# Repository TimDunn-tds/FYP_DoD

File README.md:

# FYP_DoD
Disk-on-disk FYP files.

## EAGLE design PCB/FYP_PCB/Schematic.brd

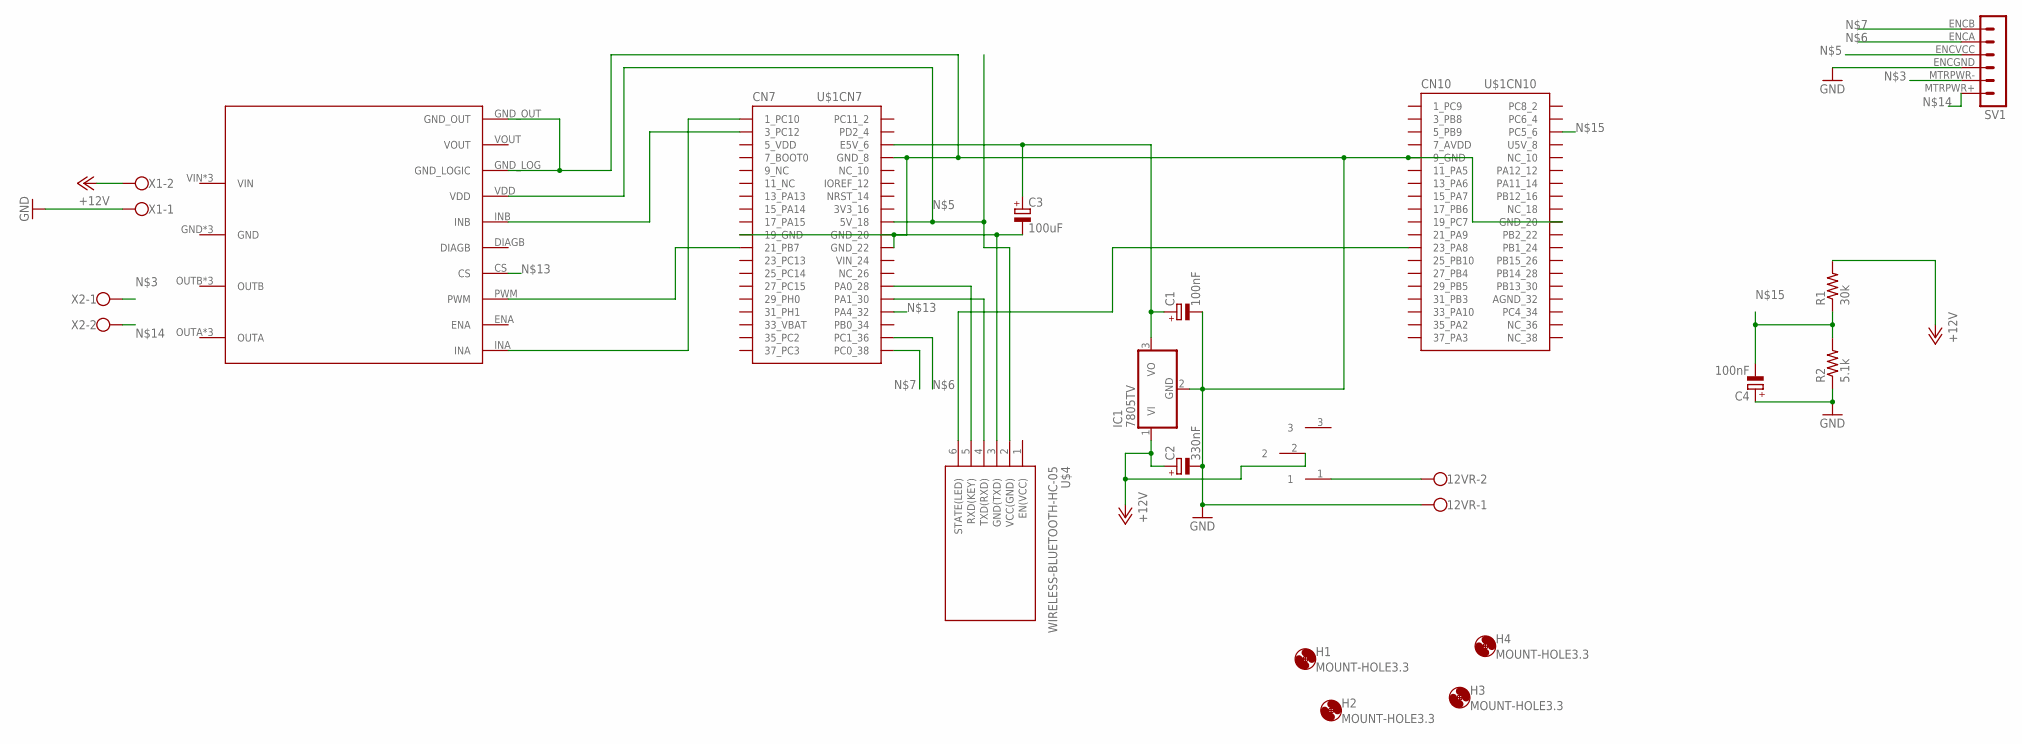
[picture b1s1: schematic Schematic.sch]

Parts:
12VR: W237-102
C1, C4: 100nF; E2,5-5
C2: 330nF; E2,5-5
C3: 100uF; E2,5-5
H1, H2, H3, H4: MOUNT-HOLE3.3; 3,3
IC1: 7805TV; TO220V
R1: 30k; 0204/7
R2: 5.1k; 0204/7
SV1: MA06-1
U$1: NUCLEO-SHIELD-20PIN; NUCLEO-SHIELD-UNDERSIDE-SHORT-20-PINHEADER
U$2: VNH5019REAL; MULTIPOWERSO-302
U$3: TOGGLESWITCH
U$4: WIRELESS-BLUETOOTH-HC-05
X1, X2: W237-102

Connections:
+12V: C2.+, IC1.1 (VI), R1.2, U$3.2, X1.2
EN(VCC): U$4.1 (EN(VCC))
GND: 12VR.1, C1.-, C2.-, C3.-, C4.+, IC1.2 (GND), R2.1, SV1.ENCGND, U$1.CN7_8 (GND_8), U$1.CN7_19 (19_GND), U$1.CN7_20 (GND_20), U$1.CN7_22 (GND_22), U$1.CN10_9 (9_GND), U$1.CN10_20 (GND_20), U$2.GND_LOG (GND_LOGIC), U$2.GND_OUT, U$4.3 (GND(TXD)), X1.1
unnamed: U$1.CN7_1 (1_PC10), U$2.INA
unnamed: U$1.CN7_21 (21_PB7), U$2.PWM
unnamed: SV1.MTRPWR-, X2.1
unnamed: U$1.CN7_3 (3_PC12), U$2.INB
unnamed: SV1.ENCVCC, U$1.CN7_18 (5V_18), U$2.VDD, U$4.2 (VCC(GND))
unnamed: SV1.ENCA, U$1.CN7_36 (PC1_36)
unnamed: SV1.ENCB, U$1.CN7_38 (PC0_38)
unnamed: 12VR.2, U$3.1
unnamed: U$1.CN7_30 (PA1_30), U$4.4 (TXD(RXD))
unnamed: C1.+, C3.+, IC1.3 (VO), U$1.CN7_6 (E5V_6)
unnamed: U$1.CN7_28 (PA0_28), U$4.5 (RXD(KEY))
unnamed: U$1.CN10_23 (23_PA8), U$4.6 (STATE(LED))
unnamed: U$1.CN7_32 (PA4_32), U$2.CS
unnamed: SV1.MTRPWR+ (MTRPWR), X2.2
unnamed: C4.-, R1.1, R2.2, U$1.CN10_6 (PC5_6)

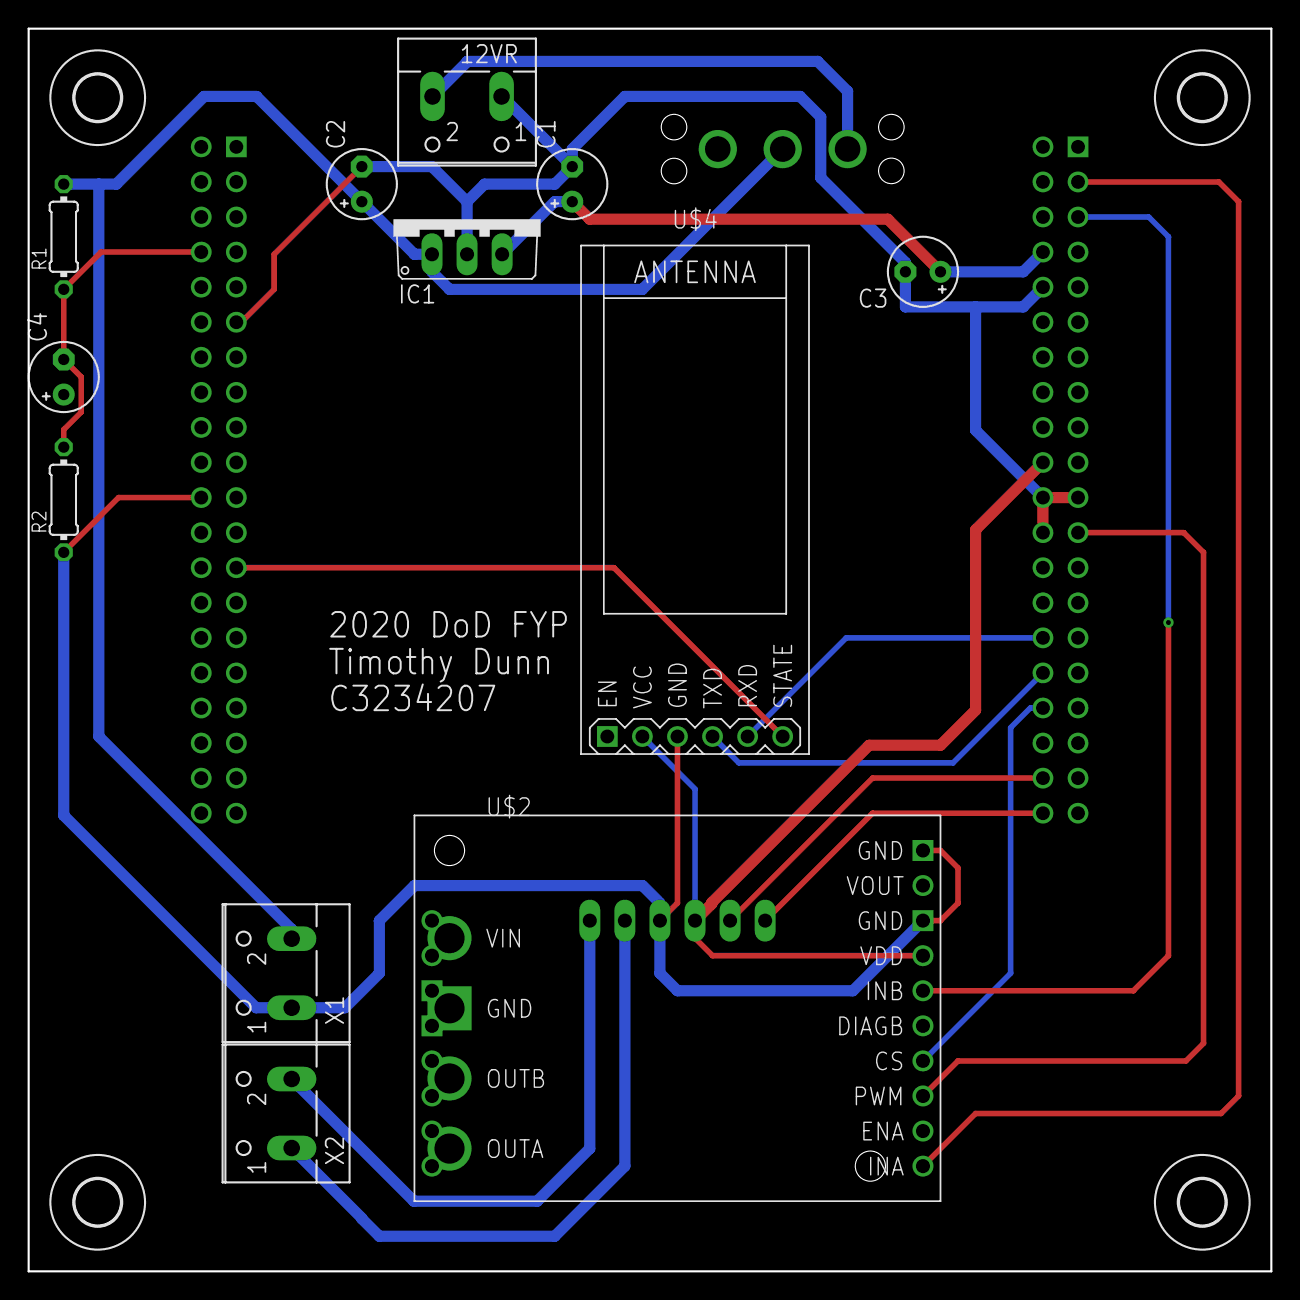
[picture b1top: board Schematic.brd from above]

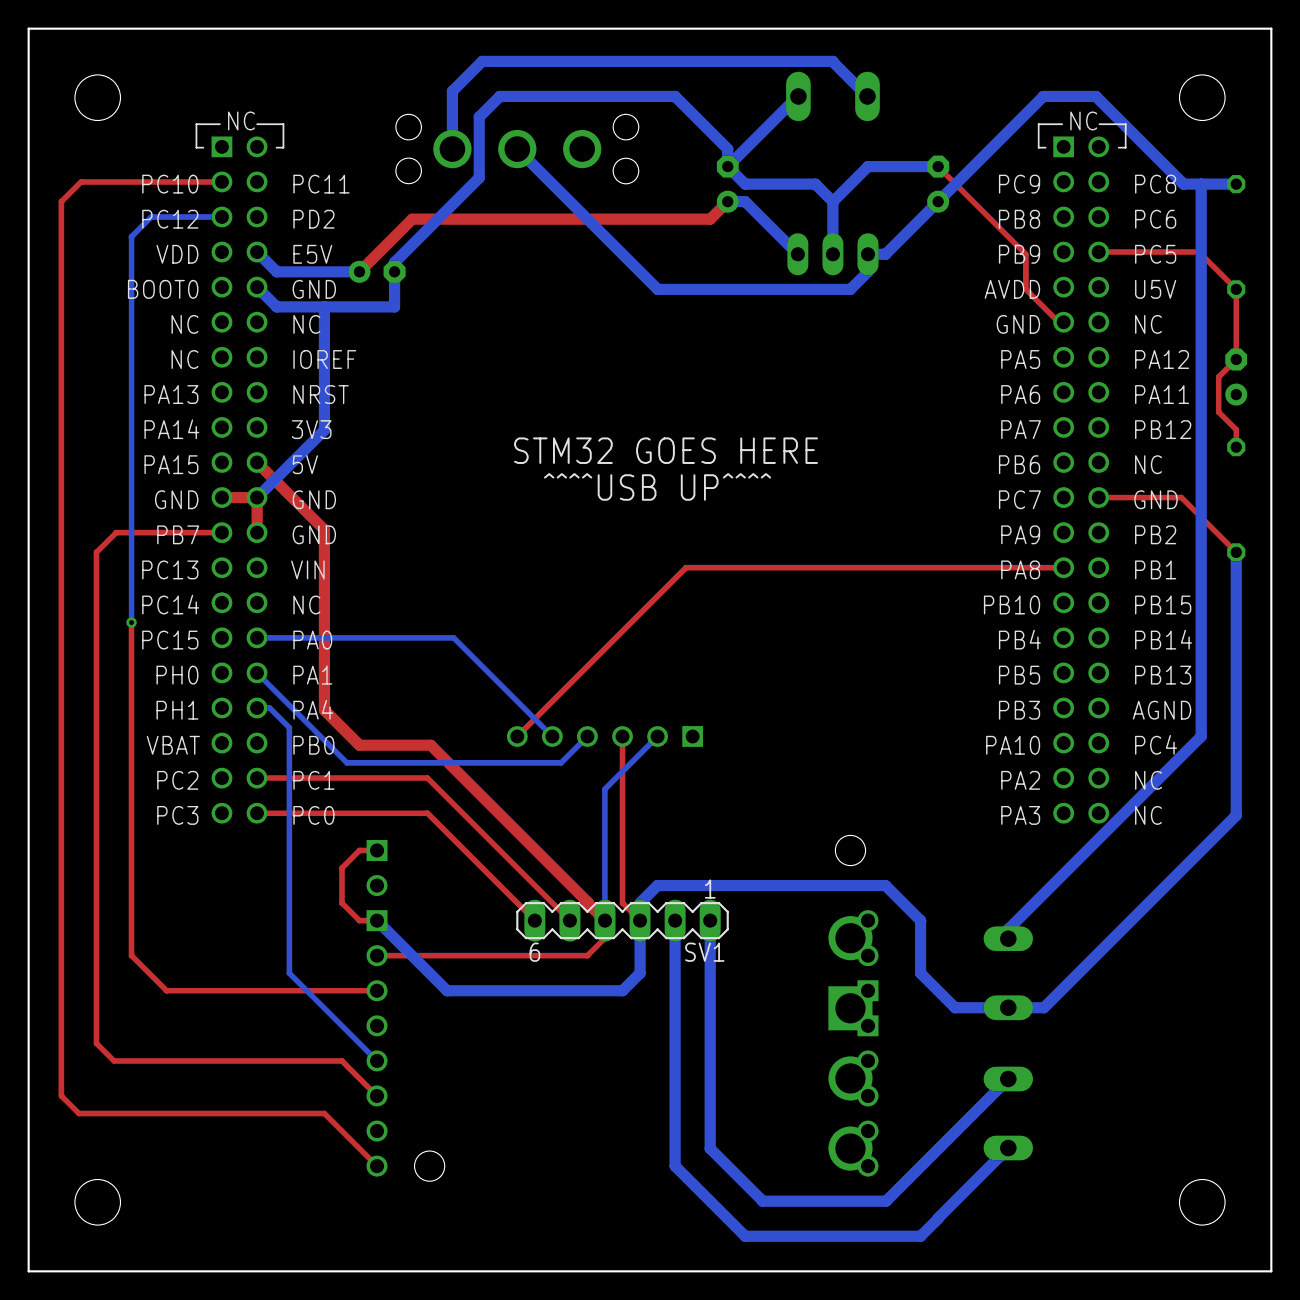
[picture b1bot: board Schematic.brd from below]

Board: 2 copper layers, 90.0 x 90.0 mm, 19 parts (2 on the bottom side), 17 nets.

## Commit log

2020-01-29 Add project description to repo.
2020-02-04 Add 2 papers to repo.
2020-02-05 Create initial simulation matlab code and simulink model.
2020-02-09 Add MPC resources. Create initial pieces of MPC
2020-02-09 Complete MPC implementation. Balance disks. Add setpoint regulation.
2020-02-09 Create visualisation of DoD system.
2020-02-12 Create 2017a compatible simulink model.
2020-02-12 Create 2016 simulink model and remove 2017 model.
2020-02-23 Add line indicating angle of object to visualisation
2020-02-24 Correct(?) equation for alpha.
2020-02-25 Begin implementing new model structure.
2020-02-26 Implement model based on an inertial theta coordinate system (hand fixed). Phi does not encompass theta.
2020-02-26 Implement inertial theta model with fixed phi. Phi encompasses theta.
2020-03-01 Attempt to figure out why MPC doesnt work.
2020-03-01 MATLAB garbage.
2020-03-01 No real changes.
2020-03-02 Reimplement my own model. Change timescale on visualisation.
2020-03-02 Implement LQG. Balance disks. Add DoD_vid to gitignore.
2020-03-09 Remove 2016 files. Make small modifications to parameters.
2020-03-09 Add pololu motor parameter script (external).
2020-03-09 Create mechanical drawings. Increase state penatlies.
2020-03-10 Create project title submission doc.
2020-03-10 Create BOM. Link axes in force/velocity plots.
2020-03-16 Fix incorrect kinematic equations and associated visulisation.
2020-03-22 Change plots to RPM.
2020-03-22 Remove git garbage.
2020-03-22 Add BOM.
2020-04-15 Did a lot of drawings.
2020-04-21 Create computer vision scripts to measure position, distance and angle of two circular shapes.
2020-04-22 Create script to detect circle position from contiunous live webcam video.
2020-04-22 Create camera params for desk drawer position. Implement undistortion of image for real-time tracking. Implement angle measuring for real-time tracking.
2020-05-19 Redesign apparatus for 400x400 max sheet size.
2020-05-24 Start report.
2020-05-25 Do more of report. Create figures for report in ppt.
2020-05-28 Write more of report. Add some CV resources.
2020-05-29 Finish sections up to design.
2020-06-01 Complete more of report. Change the plotting of some figures. Add object to assembly drawing.
2020-06-02 Create more figures.
2020-06-11 Write report. Start writing speech.
2020-06-12 Add more to background of presentation script.
2020-06-14 Flesh out background and motivation part of presentation script.
2020-06-15 Finish speech. Correct a figure in report.
2020-06-15 Complete slideshow. Complete script for presentation. Download images for presentation.
2020-06-29 Add tolerances to drawings. Create shaft and coupling drawing.
2020-07-08 Commit to move house,
2020-07-22 Create PCB. Amend drawings for 380x300. Change CV to new house setup.
2020-07-22 Get STM32 to working state.
2020-07-22 Remove unneeded C files. Create simulation directory.
2020-07-30 Update gitignore to ignore eagle backup files(?)
2020-07-30 Update PCB for new pin configurations. Add HC05 bluetooth module.
2020-07-30 Create voltage divider files.
2020-07-30 Implement DC motor control
2020-07-30 Garbage I dont want but cant get rid of without errors.
2020-07-30 Implement serial communication in matlab.
2020-07-30 Implement ADC for DC motor.
2020-07-30 Add new commands to command parser. Implement encoder. Change serial to wired connection.
2020-07-30 Create log data command for dc motor parameter estimisation.
2020-07-30 Update frame drawing. Calculate moments of inertia for some components.
2020-07-30 Eagle garbage I cant gitignore.
2020-07-30 Update moment of inertiate to reflect real values.
2020-07-31 Implement ADC as voltmeter for source voltage.
2020-07-31 Update PCB to put CS on an ADC pin.
2020-07-31 Setup ADC for current sense. Create sysID inputs and data logger.
2020-08-02 Create input data for sysID. Write mutlivariable minimisation solver for parameters. Create linear motor model.
2020-08-04 Add mounting holes to flat bar for motor. Amend motor bracket.
2020-08-04 Create sysID parameter estimation scripts.
2020-08-05 Add different friction models to sysID. (Can also be labelled: Beat head against wall with sysID)
2020-08-12 *WIP* Create scripts for sysID up to non-linear step.
2020-08-12 Change PCB layout and generate gerber files for production.
2020-08-12 Change method of polling sensors to ensure consistency.
2020-08-14 Backup before windows rollback.
2020-08-19 Push to change computers
2020-08-20 Add inertia as estimated parameter. Add hysterisi firction function.
2020-08-26 Push to change to laptop.
2020-08-27 Add control allocation to simulink model.
2020-08-27 Update CV for experiment rig.
2020-08-27 Add soft voltage max. Make time printout robots when logging data.
2020-08-27 Add some comments.
2020-08-27 Write scripts to run experiment.
2020-09-04 Lots of things. Getting nervous about state of my computer.
2020-09-09 Move to laptop
2020-09-09 Change to velocity control from torque control. Backup most torque files.
2020-09-30 Laptop transfer
2020-09-30 Forgot to save.
2020-10-13 Backup FYP B Report.
2020-10-18 Backup report.
2020-10-19 Backup presentation and powerpoint
2020-10-21 Push to record on laptop
2020-11-02 Report backup. This isnt how you are supposed to use git.
2020-11-04 Finish FYP Report.
2020-11-12 Complete report.
2020-11-26 Push for presentation.
